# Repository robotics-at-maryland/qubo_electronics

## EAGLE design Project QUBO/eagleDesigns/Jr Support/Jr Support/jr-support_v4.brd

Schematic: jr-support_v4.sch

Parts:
2PIN_1, 2PIN_2, 2PIN_3, 2PIN_5: KK254_VERT_2PIN""; KK254_VERT_2PIN
3V3_LED, 5V_LED, 12V_LED: 0805_LED; 0805
5V_CURR_ADC, 12V_CURR_ADC: ADC121C021; VSSOP-8
5V_OUT: 5V_OUT; KK254_VERT_2PIN
5V_VOLTAGE, 12V_VOLTAGE: INA219SOT23; SOT-23-8
12V_OUT: 12V_OUT; KK254_VERT_2PIN
AUDIO, AUDIO1: KK254_VERT_2PIN""; KK254_VERT_2PIN
BATT1_IN, BATT2_IN: KK254_VERT_2PIN""; KK254_VERT_2PIN
BME280: BME280; BME280_LGA
C1, C2, C5, C7, C8, C10, C11, C13, C14, C16, C17, C19, C21, C22, C23, C33, C46, C47, C59, C64, C69, C70, C71, C72, C73, C74, C77, C79, C80, C81, C84, C94, C101, C103, C104, C106, C107, C109, C110, C112, C113: 0.1u; C0805
C3, C6, C9, C12, C15, C18, C20, C29, C31, C37, C57: 47n; C0805
C4, C27: 0.22u; C0805
C24, C25, C26: 100n; C0805
C28, C65: 22u; C0805
C30: 4.7n; C0805
C34, C35, C36, C60, C66, C93: 1u; C0805
C38, C50: 330 uF; CKR_D10
C40, C51: .1 uF; C0805
C43, C44: 100u; 140CLH-0810
C45, C82, C85: 1n; C0805
C48, C49, C61, C62, C75, C76, C88, C102, C105, C108, C111, C114: 10u; C0805
C53, C78, C83: 4.7u; C0805
CAMERA1, CAMERA2: KK254_VERT_2PIN""; KK254_VERT_2PIN
CIN1, CIN2, CIN3, CIN4: 2.2 uF; C1210
CPU_PWR: CPU PWR; KK254_VERT_4PIN
DEPTH_SENS: Depth Sensor; KK254_VERT_4PIN
ETHERNET: KK254_VERT_2PIN""; KK254_VERT_2PIN
FAN1, FAN2: KK254_VERT_2PIN""; KK254_VERT_2PIN
JP1, JP2: JP1E; JP1
JP3, JP4, JP5, JP6: PINHD-1X2; 1X02
LED1, LED3: Red; 0805
LED4: Green; CHIPLED_0805
LED5, LED8, LED9: Green; 0805
LED6, LED7: Yellow; 0805
PMOS1, PMOS2: SSM3J353F; SOT-346-3/S-MINI
R2, R3: R-TRIMM3314J; RTRIM3314J
R4: 10k; R0805
R5: 21kO; RC55
R6: 2.61kO; RC55
R7, R8: 4.7k; R0805
R9: 12k; R0805
R10, R11: 4.2k; R0805
R12, R15: 5m; R0805
R13: 20.8k; R0805
R14, R23: 51k; R0805
R16, R26: 10\; R0805
R17, R27: 200k; R0805
R19, R28: 8.2k; R0805
R20, R24: 5.1k; R0805
R22: 510; R0805
R25, R30, R35: 10; R0805
R29: 6.8k; R0805
R31: 270; R0805
R32, R50, R51: 1.5k; R0805
R33, R44, R46: 1.2k; R0805
R34: 68; R0805
R36, R41, R45, R47: 1MO; R0805
R37, R42: 430; R0805
R39, R43, R48, R49: 330; R0805
SHORE_IN: KK254_VERT_2PIN""; KK254_VERT_2PIN
TEST-PTS, TEST-PTS1: 0; V526-0
THRUST1, THRUST2, THRUST3, THRUST4, THRUST5, THRUST6, THRUST7, THRUST8: KK254_VERT_4PIN22-29-2041; KK254_VERT_4PIN
THRUSTER_CURR_ADC: ADS7828; TSSOP16
U1: PCA9685; TSSOP-28_4MM
U$1, U$45, U$63, U$64, U$66: VTVSDO-219AB; DO-219AB
U$2, U$4, U$8, U$11, U$14, U$17, U$19, U$23, U$29, U$35, U$39: ACS713SOIC; ACS713-SOIC
U$3, U$54, U$69, U$70, U$71, U$72, U$73, U$74, U$75, U$76: TEST_PT534-5004; 534-5004
U$5: 25A Fuse; 1.25"_FUSECLIPS
U$6, U$9, U$12, U$15, U$18, U$20, U$27, U$36, U$37, U$40: 4A Fuse; 154-OMNI-BLOK
U$7: KUHP-5XX1-XX; KUHP_6.35MM-QUICK-CONNECT
U$10, U$13, U$16, U$21, U$22, U$26, U$28, U$30, U$31, U$32, U$33, U$34, U$38, U$42, U$43, U$44, U$46, U$47, U$62, U$67, U$68: VTVSSOT323; SOT323-R
U$24: BTS5090-1EJA; SOIC8+PAD
U$25, U$41: PTN78060W
U$48, U$51: LTC4364MSOP; MSOP16
U$49, U$50, U$52, U$53: STD95N2LH5; DPAK
U$55, U$58: BSS138CT-NDSOT23; SOT23
U$56: 74LVC1G14; TSSOP5
U$57: NCP1117; SOT-223
U$60, U$61: TL431DBZ; SOT-23-3
V-THRUST_CURR_ADC: ADC121C021; VSSOP-8
V-THRUST_LED: 0805_LED; 0805
V-THRUST_OUT: Vin_OUT; KK254_VERT_2PIN
V-THRUST_VOLTAGE: INA219SOT23; SOT-23-8

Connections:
5V: C36.1, C62.1, JP3.1, R29.2, U$56.P$5 (VDD), U$57.P$2 (VOUT), U$57.P$4 (VOUT)
5V_CURR: C50.P$1 (+), C51.1, U$2.P$1 (IP+), U$2.P$2 (IP+), U$25.P$5 (VO), U$25.P$7 (VOSENSE)
12V_CURR: C38.P$1 (+), C40.1, U$35.P$1 (IP+), U$35.P$2 (IP+), U$41.P$5 (VO), U$41.P$7 (VOSENSE)
+3V3: 2PIN_2.P$1, BME280.P$2 (!CS), BME280.P$5 (SDO/ADR), BME280.P$6 (VDDIO), BME280.P$8 (VDD), C24.1, C25.1, C26.1, C83.1, C84.1, C85.1, R10.2, R11.2, R34.2, U$3.P$1
+5V: 2PIN_1.P$1, 2PIN_3.P$1, 5V_CURR_ADC.P$5 (VDD), 5V_CURR_ADC.P$6 (ADR1), 5V_OUT.P$1, 5V_VOLTAGE.P$4 (VS), 12V_CURR_ADC.P$5 (VDD), 12V_VOLTAGE.P$4 (VS), 12V_VOLTAGE.P$8 (A1), C1.1, C2.1, C5.1, C7.1, C8.1, C11.1, C13.1, C14.1, C19.1, C48.1, C53.1, C59.1, C64.1, C66.1, C69.1, C70.1, C71.1, C72.1, C73.1, C79.1, C81.1, C82.1, C93.1, C94.1, C103.1, C106.1, C109.1, C112.1, DEPTH_SENS.P$4, ETHERNET.P$1, FAN1.P$1, FAN2.P$1, R7.2, R8.2, R31.2, R35.1, THRUSTER_CURR_ADC.10 (REF), THRUSTER_CURR_ADC.16 (VDD), U1.1 (A0), U1.2 (A1), U1.3 (A2), U1.4 (A3), U1.5 (A4), U1.24 (A5), U1.28 (VDD), U$2.P$8 (VCC), U$4.P$8 (VCC), U$8.P$8 (VCC), U$11.P$8 (VCC), U$14.P$8 (VCC), U$17.P$8 (VCC), U$19.P$8 (VCC), U$20.P$2, U$21.1 (C), U$21.2 (C), U$23.P$8 (VCC), U$29.P$8 (VCC), U$35.P$8 (VCC), U$39.P$8 (VCC), U$42.1 (C), U$42.2 (C), U$43.1 (C), U$43.2 (C), U$44.1 (C), U$44.2 (C), U$46.1 (C), U$46.2 (C), U$47.1 (C), U$47.2 (C), U$69.P$1, V-THRUST_CURR_ADC.P$3 (ADR0), V-THRUST_CURR_ADC.P$5 (VDD), V-THRUST_CURR_ADC.P$6 (ADR1), V-THRUST_VOLTAGE.P$4 (VS), V-THRUST_VOLTAGE.P$7 (A0), V-THRUST_VOLTAGE.P$8 (A1)
+12V: 12V_OUT.P$1, C16.1, C33.1, C45.1, C49.1, C77.1, C78.1, CPU_PWR.P$3, CPU_PWR.P$4, JP4.1, R25.1, R33.2, U$1.P$2 (C), U$24.PAD (VS), U$36.P$2, U$63.P$2 (C), U$64.P$2 (C), U$70.P$1
GND: 2PIN_2.P$2, 2PIN_3.P$2, 2PIN_5.P$2, 3V3_LED.P$2 (C), 5V_CURR_ADC.P$3 (ADR0), 5V_CURR_ADC.P$7 (GND), 5V_LED.P$2 (C), 5V_OUT.P$2, 5V_VOLTAGE.P$3 (GND), 5V_VOLTAGE.P$7 (A0), 5V_VOLTAGE.P$8 (A1), 12V_CURR_ADC.P$3 (ADR0), 12V_CURR_ADC.P$6 (ADR1), 12V_CURR_ADC.P$7 (GND), 12V_LED.P$2 (C), 12V_OUT.P$2, 12V_VOLTAGE.P$3 (GND), 12V_VOLTAGE.P$7 (A0), AUDIO.P$2, AUDIO1.P$2, BATT1_IN.P$2, BATT2_IN.P$2, BME280.P$1 (GND1), BME280.P$7 (GND2), C1.2, C2.2, C3.2, C4.2, C5.2, C6.2, C7.2, C8.2, C9.2, C10.2, C11.2, C12.2, C13.2, C14.2, C15.2, C16.2, C17.2, C18.2, C19.2, C20.2, C21.2, C22.2, C23.2, C24.2, C25.2, C26.2, C27.2, C28.2, C29.2, C30.2, C31.2, C33.2, C34.2, C35.2, C36.2, C37.2, C38.P$2 (-), C40.2, C43.-, C44.-, C45.2, C46.2, C47.2, C48.2, C49.2, C50.P$2 (-), C51.2, C53.2, C57.2, C59.2, C60.2, C61.2, C62.2, C64.2, C65.2, C66.2, C69.2, C70.2, C71.2, C72.2, C73.2, C74.2, C75.2, C76.2, C77.2, C78.2, C79.2, C80.2, C81.2, C82.2, C83.2, C84.2, C85.2, C88.2, C93.2, C94.2, C101.2, C102.2, C103.2, C104.2, C105.2, C106.2, C107.2, C108.2, C109.2, C110.2, C111.2, C112.2, C113.2, C114.2, CAMERA1.P$2, CAMERA2.P$2, CIN1.2, CIN2.2, CIN3.2, CIN4.2, CPU_PWR.P$1, CPU_PWR.P$2, DEPTH_SENS.P$3, ETHERNET.P$2, FAN1.P$2, FAN2.P$2, JP1.1, JP2.1, LED1.P$2 (C), LED3.P$2 (C), LED6.P$2 (C), LED7.P$2 (C), LED8.P$2 (C), LED9.P$2 (C), R2.1 (E), R3.1 (E), R4.1, R5.P$2 (2), R6.P$2 (2), R9.1, R13.1, R20.1, R24.1, SHORE_IN.P$2, TEST-PTS.1, TEST-PTS1.1, THRUST1.P$1, THRUST1.P$3, THRUST2.P$1, THRUST2.P$3, THRUST3.P$1, THRUST3.P$3, THRUST4.P$1, THRUST4.P$3, THRUST5.P$1, THRUST5.P$3, THRUST6.P$1, THRUST6.P$3, THRUST7.P$1, THRUST7.P$3, THRUST8.P$1, THRUST8.P$3, THRUSTER_CURR_ADC.9 (GND), THRUSTER_CURR_ADC.11 (COM), THRUSTER_CURR_ADC.12 (A0), THRUSTER_CURR_ADC.13 (A1), U1.14 (VSS), U1.23 (!OE), U1.25 (EXTCLK), U$1.P$1 (A), U$2.P$5 (GND), U$4.P$5 (GND), U$7.5A (5), U$7.5B (5), U$7.BA (B), U$7.BB (B), U$8.P$5 (GND), U$10.3 (A), U$11.P$5 (GND), U$13.3 (A), U$14.P$5 (GND), U$16.3 (A), U$17.P$5 (GND), U$19.P$5 (GND), U$22.3 (A), U$23.P$5 (GND), U$24.1 (GND), U$25.P$1 (GND1), U$25.P$2 (GND2), U$26.3 (A), U$28.3 (A), U$29.P$5 (GND), U$30.3 (A), U$31.3 (A), U$32.3 (A), U$33.3 (A), U$34.3 (A), U$35.P$5 (GND), U$38.3 (A), U$39.P$5 (GND), U$41.P$1 (GND1), U$41.P$2 (GND2), U$42.3 (A), U$43.3 (A), U$44.3 (A), U$45.P$1 (A), U$46.3 (A), U$47.3 (A), U$48.GND, U$48.OV, U$51.GND, U$51.OV, U$55.2 (S), U$56.P$3 (GND), U$57.P$1 (GND), U$58.2 (S), U$60.P$3 (A), U$61.P$3 (A), U$62.3 (A), U$63.P$1 (A), U$64.P$1 (A), U$66.P$1 (A), U$67.3 (A), U$68.3 (A), V-THRUST_CURR_ADC.P$7 (GND), V-THRUST_LED.P$2 (C), V-THRUST_OUT.P$2, V-THRUST_VOLTAGE.P$3 (GND)
unnamed: R26.1, U$48.HGATE
unnamed: C30.1, JP4.2, U$7.AA (A), U$7.AB (A), U$24.6 (OUT), U$24.7 (OUT), U$24.8 (OUT), U$45.P$2 (C)
unnamed: JP2.2, U$41.P$3 (!INHIBIT!)
unnamed: 2PIN_1.P$2, C23.1, R4.2, U$21.3 (A), U$24.2 (IN)
unnamed: R6.P$1 (1), U$41.P$6 (VOADJUST)
unnamed: C3.1, U$2.P$6 (FILTER)
unnamed: C9.1, U$8.P$6 (FILTER)
unnamed: C6.1, U$4.P$6 (FILTER)
unnamed: JP1.2, U$25.P$3 (!INHIBIT!)
unnamed: U$4.P$3 (IP-), U$4.P$4 (IP-), U$6.P$1
unnamed: R5.P$1 (1), U$25.P$6 (VOADJUST)
unnamed: U$8.P$3 (IP-), U$8.P$4 (IP-), U$9.P$1
unnamed: C12.1, U$11.P$6 (FILTER)
unnamed: C4.1, U$48.TMR
unnamed: U$11.P$3 (IP-), U$11.P$4 (IP-), U$12.P$1
unnamed: C15.1, U$14.P$6 (FILTER)
unnamed: R23.2, R28.1
unnamed: R26.2, U$49.1 (G)
unnamed: U$14.P$3 (IP-), U$14.P$4 (IP-), U$15.P$1
unnamed: C18.1, U$17.P$6 (FILTER)
unnamed: R12.1, U$48.SENSE, U$50.TAB (D)
unnamed: U$17.P$3 (IP-), U$17.P$4 (IP-), U$18.P$1
unnamed: C29.1, U$23.P$6 (FILTER)
unnamed: U$48.DGATE, U$50.1 (G)
unnamed: U$23.P$3 (IP-), U$23.P$4 (IP-), U$27.P$1
unnamed: C37.1, U$29.P$6 (FILTER)
unnamed: C20.1, U$19.P$6 (FILTER)
unnamed: U$5.P$1, U$5.P$2, U$19.P$3 (IP-), U$19.P$4 (IP-)
unnamed: R13.2, R17.1, U$51.UV
unnamed: R14.1, R20.2, U$51.FB
unnamed: U$29.P$3 (IP-), U$29.P$4 (IP-), U$37.P$1
unnamed: C57.1, U$39.P$6 (FILTER)
unnamed: R9.2, R27.1, U$48.UV
unnamed: R16.1, U$51.HGATE
unnamed: C27.1, U$51.TMR
unnamed: R14.2, R19.1
unnamed: R16.2, U$52.1 (G)
unnamed: U$51.SOURCE, U$52.3 (S), U$53.3 (S)
unnamed: R15.1, U$51.SENSE, U$53.TAB (D)
unnamed: U$39.P$3 (IP-), U$39.P$4 (IP-), U$40.P$1
unnamed: U$51.DGATE, U$53.1 (G)
unnamed: 12V_VOLTAGE.P$1 (IN+), 12V_VOLTAGE.P$2 (IN-), R25.2
unnamed: R23.1, R24.2, U$48.FB
unnamed: C60.1, R22.2, U$56.P$2 (IN)
unnamed: C31.1, U$35.P$6 (FILTER)
unnamed: U$19.P$7 (VIOUT), V-THRUST_CURR_ADC.P$4 (VIN)
unnamed: U$48.SOURCE, U$49.3 (S), U$50.3 (S)
unnamed: U$2.P$3 (IP-), U$2.P$4 (IP-), U$20.P$1
unnamed: U$35.P$3 (IP-), U$35.P$4 (IP-), U$36.P$1
unnamed: 5V_CURR_ADC.P$4 (VIN), U$2.P$7 (VIOUT)
unnamed: R30.2, V-THRUST_VOLTAGE.P$1 (IN+), V-THRUST_VOLTAGE.P$2 (IN-)
unnamed: 12V_CURR_ADC.P$4 (VIN), U$35.P$7 (VIOUT)
unnamed: JP3.2, U$48.SHDN (!SHDN!), U$51.SHDN (!SHDN!), U$56.P$4 (OUT)
unnamed: LED1.P$1 (A), R37.1
unnamed: PMOS1.P$1 (G), R36.1, U$51.FLT (!FAULT!)
unnamed: AUDIO.P$1, R37.2, R39.1
unnamed: LED3.P$1 (A), R42.1
unnamed: PMOS2.P$1 (G), R41.1, U$48.FLT (!FAULT!)
unnamed: AUDIO1.P$1, R42.2, R43.1
unnamed: R44.1, U$55.3 (D)
unnamed: LED4.C, R44.2
unnamed: 5V_LED.P$1 (A), R31.1
unnamed: R32.1, V-THRUST_LED.P$1 (A)
unnamed: 12V_LED.P$1 (A), R33.1
unnamed: 3V3_LED.P$1 (A), R34.1
unnamed: R46.1, U$58.3 (D)
unnamed: LED5.P$2 (C), R46.2
unnamed: 5V_VOLTAGE.P$1 (IN+), 5V_VOLTAGE.P$2 (IN-), R35.2
unnamed: R2.2 (S), TEST-PTS.2, U$60.P$2 (REF)
unnamed: LED6.P$1 (A), R48.1, U$60.P$1 (C)
unnamed: R3.2 (S), TEST-PTS1.2, U$61.P$2 (REF)
unnamed: LED7.P$1 (A), R49.1, U$61.P$1 (C)
unnamed: R47.1, U$51.ENOUT, U$58.1 (G)
unnamed: R45.1, U$48.ENOUT, U$55.1 (G)
unnamed: LED8.P$1 (A), R50.1
unnamed: LED9.P$1 (A), R51.1
unnamed: PMOS1.P$2 (D), R39.2
unnamed: PMOS2.P$2 (D), R43.2
SCL: 5V_CURR_ADC.P$1 (SCL), 5V_VOLTAGE.P$5 (SCL), 12V_CURR_ADC.P$1 (SCL), 12V_VOLTAGE.P$5 (SCL), JP5.2, R8.1, THRUSTER_CURR_ADC.14 (SCL), U1.26 (SCL), U$71.P$1, V-THRUST_CURR_ADC.P$1 (SCL), V-THRUST_VOLTAGE.P$5 (SCL)
SCL-3V3: BME280.P$4 (SCK/SCL), DEPTH_SENS.P$1, JP6.2, R11.1
SDA: 5V_CURR_ADC.P$8 (SDA), 5V_VOLTAGE.P$6 (SDA), 12V_CURR_ADC.P$8 (SDA), 12V_VOLTAGE.P$6 (SDA), JP5.1, R7.1, THRUSTER_CURR_ADC.15 (SDA), U1.27 (SDA), U$72.P$1, V-THRUST_CURR_ADC.P$8 (SDA), V-THRUST_VOLTAGE.P$6 (SDA)
SDA-3V3: BME280.P$3 (SDI/SDA), DEPTH_SENS.P$2, JP6.1, R10.1
SHDN_SW: 2PIN_5.P$1, R22.1, R29.1, U$62.1 (C), U$62.2 (C)
T1_CURR: THRUSTER_CURR_ADC.1 (CH0), U$4.P$7 (VIOUT)
T1_PWM: THRUST1.P$2, U1.6 (CH0)
T2_CURR: THRUSTER_CURR_ADC.2 (CH1), U$8.P$7 (VIOUT)
T2_PWM: THRUST2.P$2, U1.7 (CH1)
T3_CURR: THRUSTER_CURR_ADC.3 (CH2), U$11.P$7 (VIOUT)
T3_PWM: THRUST3.P$2, U1.8 (CH2)
T4_CURR: THRUSTER_CURR_ADC.4 (CH3), U$14.P$7 (VIOUT)
T4_PWM: THRUST4.P$2, U1.9 (CH3)
T5_CURR: THRUSTER_CURR_ADC.5 (CH4), U$17.P$7 (VIOUT)
T5_PWM: THRUST5.P$2, U1.10 (CH4)
T6_CURR: THRUSTER_CURR_ADC.6 (CH5), U$23.P$7 (VIOUT)
T6_PWM: THRUST6.P$2, U1.11 (CH5)
T7_CURR: THRUSTER_CURR_ADC.7 (CH6), U$29.P$7 (VIOUT)
T7_PWM: THRUST7.P$2, U1.12 (CH6)
T8_CURR: THRUSTER_CURR_ADC.8 (CH7), U$39.P$7 (VIOUT)
T8_PWM: THRUST8.P$2, U1.13 (CH7)
VIN: C28.1, C65.1, CIN1.1, CIN2.1, CIN3.1, CIN4.1, R12.2, R15.2, R19.2, R28.2, SHORE_IN.P$1, U$7.2A (2), U$7.2B (2), U$25.P$4 (VI), U$41.P$4 (VI), U$48.OUT, U$51.OUT, U$66.P$2 (C), U$73.P$1
V_BATT1: BATT1_IN.P$1, C34.1, C61.1, LED4.A, PMOS2.P$3 (S), R3.3 (A), R27.2, R41.2, R45.2, R49.2, R51.2, U$48.VCC, U$49.TAB (D), U$57.P$3 (VIN), U$68.1 (C), U$68.2 (C), U$75.P$1
V_BATT2: BATT2_IN.P$1, C35.1, LED5.P$1 (A), PMOS1.P$3 (S), R2.3 (A), R17.2, R36.2, R47.2, R48.2, R50.2, U$51.VCC, U$52.TAB (D), U$67.1 (C), U$67.2 (C), U$74.P$1
V_RELAY: U$7.7A (7), U$7.7B (7), U$19.P$1 (IP+), U$19.P$2 (IP+)
V_THRUST: C17.1, C21.1, C22.1, C43.+, C44.+, C46.1, C47.1, CAMERA1.P$1, CAMERA2.P$1, R30.1, R32.2, U$4.P$1 (IP+), U$4.P$2 (IP+), U$5.P$3, U$5.P$4, U$8.P$1 (IP+), U$8.P$2 (IP+), U$11.P$1 (IP+), U$11.P$2 (IP+), U$14.P$1 (IP+), U$14.P$2 (IP+), U$17.P$1 (IP+), U$17.P$2 (IP+), U$23.P$1 (IP+), U$23.P$2 (IP+), U$29.P$1 (IP+), U$29.P$2 (IP+), U$32.1 (C), U$32.2 (C), U$33.1 (C), U$33.2 (C), U$34.1 (C), U$34.2 (C), U$38.1 (C), U$38.2 (C), U$39.P$1 (IP+), U$39.P$2 (IP+), U$54.P$1, U$76.P$1, V-THRUST_OUT.P$1
V_THRUST1: THRUST1.P$4, U$6.P$2, U$31.1 (C), U$31.2 (C)
V_THRUST2: C10.1, C74.1, C75.1, C76.1, THRUST2.P$4, U$9.P$2, U$30.1 (C), U$30.2 (C)
V_THRUST3: C107.1, C108.1, THRUST3.P$4, U$12.P$2, U$26.1 (C), U$26.2 (C)
V_THRUST4: C80.1, C88.1, THRUST4.P$4, U$15.P$2, U$28.1 (C), U$28.2 (C)
V_THRUST5: C110.1, C111.1, THRUST5.P$4, U$18.P$2, U$22.1 (C), U$22.2 (C)
V_THRUST6: C101.1, C102.1, THRUST6.P$4, U$13.1 (C), U$13.2 (C), U$27.P$2
V_THRUST7: C113.1, C114.1, THRUST7.P$4, U$16.1 (C), U$16.2 (C), U$37.P$2
V_THRUST8: C104.1, C105.1, THRUST8.P$4, U$10.1 (C), U$10.2 (C), U$40.P$2

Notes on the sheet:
Address: 1110111 (0x77)(BME)
Address: 1001000 (Thrust ADC)
Address: 1010101 (12V ADC)
Address: 1011010 (VIN ADC)
Address: 1011001 (5V ADC)
12V DC/DC Converter
12V Current Sensor and 12V Net
12V Voltage sensor
12V Rail
5V Voltage Sensor
5V Current Sensor and 5V Net
5V DC/DC Converter
5V Rail
V_Thrust Rail
V_Thrust Current Sensor and V_Thrust Net
V_Thrust Voltage Sensor
Thrusters
Thruster Support
Pulling Rs
LEDs
Input Voltage
Temp Sensor
External Connectors
Thruster Relay
The blue LED will turn on when the battery voltage drops below a level given by: (2.5V)(10kO) ----------------- POT where POT is the resistance of the potentiometer.
Embedded System Headers

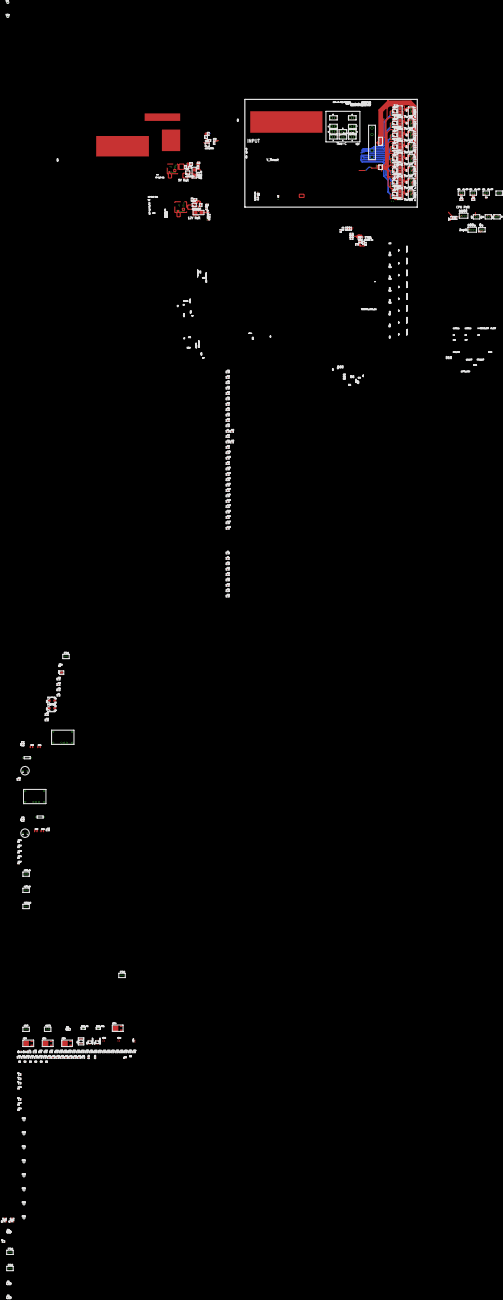
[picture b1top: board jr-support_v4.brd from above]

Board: 2 copper layers, 203.2 x 127.0 mm, 272 parts (0 on the bottom side), 119 nets.

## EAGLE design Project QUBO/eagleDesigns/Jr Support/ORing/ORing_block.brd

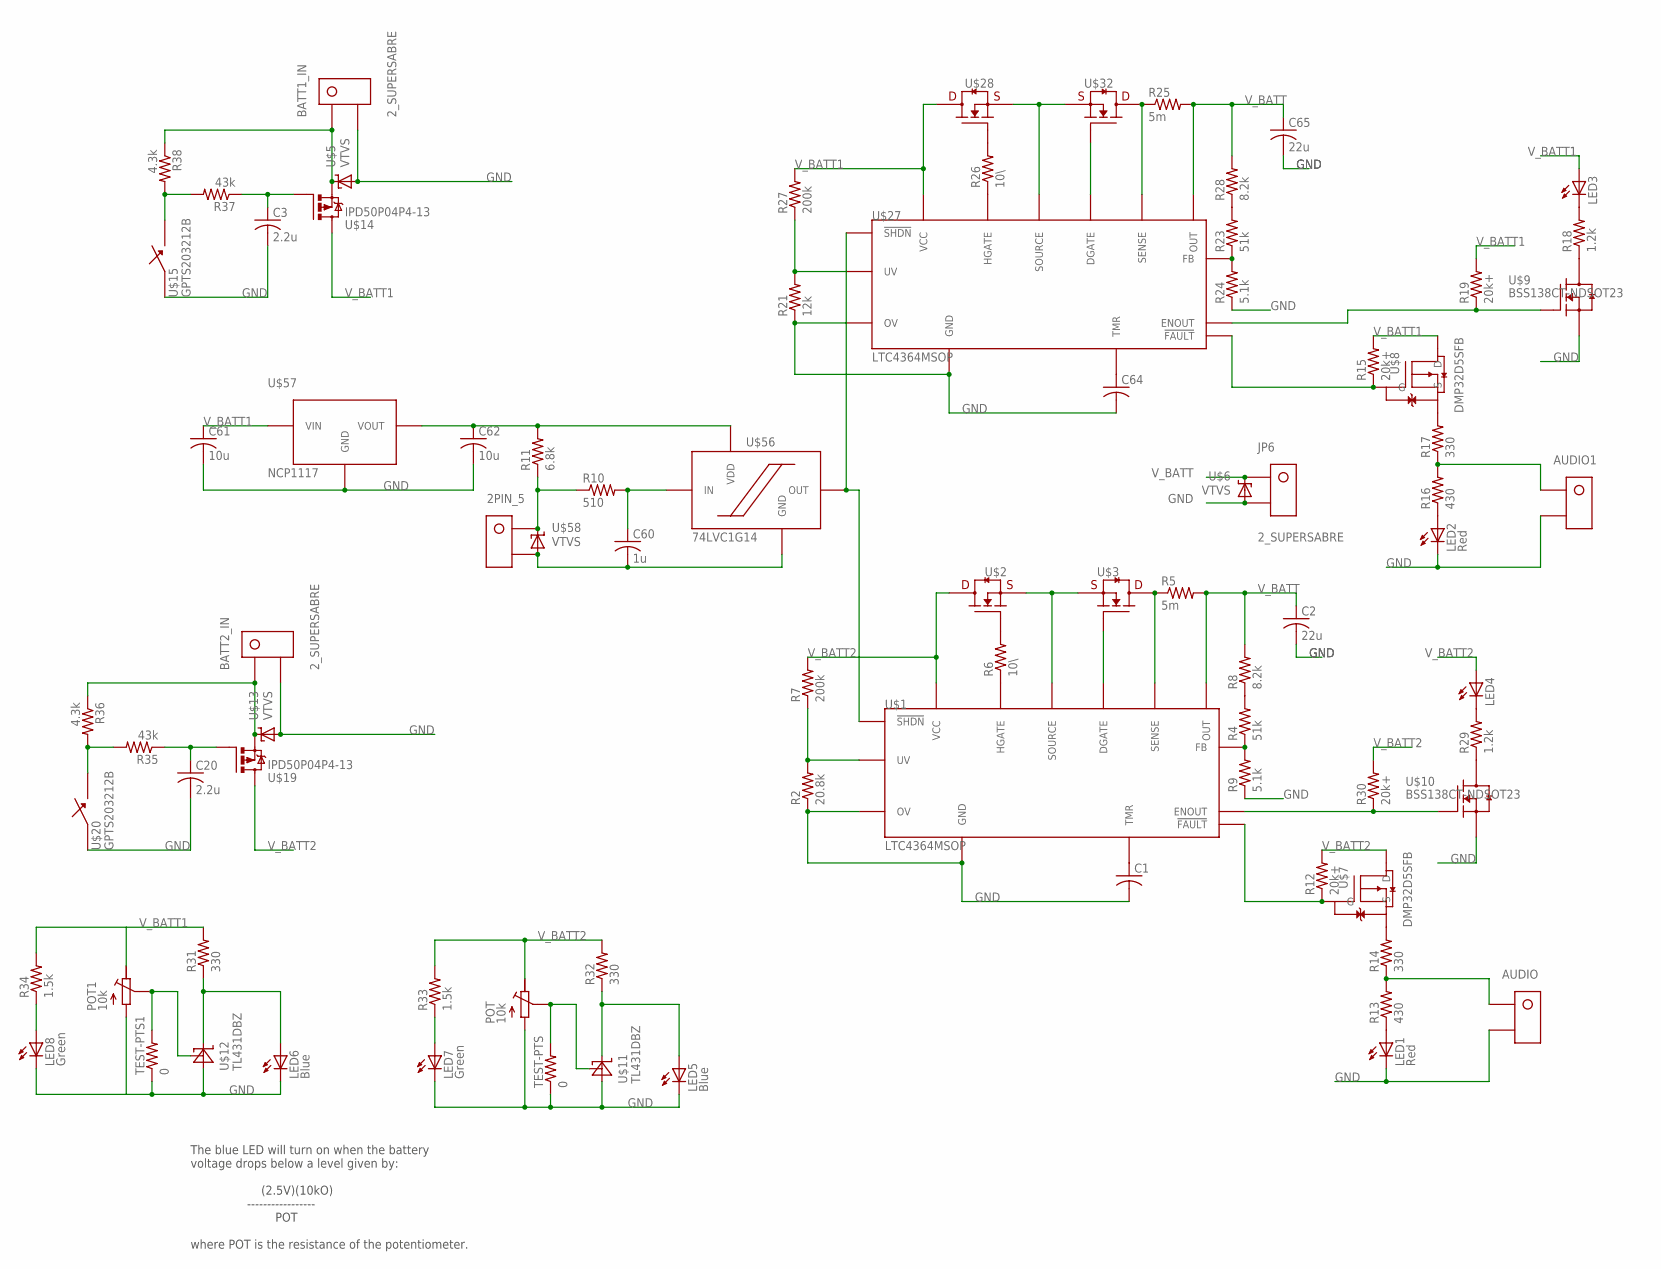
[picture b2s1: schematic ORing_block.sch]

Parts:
2PIN_5: KK254_VERT_2PIN22-29-2021; KK254_VERT_2PIN
AUDIO, AUDIO1: KK254_VERT_2PIN22-29-2021; KK254_VERT_2PIN
BATT1_IN, BATT2_IN: 2_SUPERSABRE; SUPERSABRE_2CIRCUIT
C1, C64: C-USC0805; C0805
C2, C65: 22u; C0805
C3, C20: 2.2u; C0805
C60: 1u; C0805
C61, C62: 10u; C0805
JP6: 2_SUPERSABRE; SUPERSABRE_2CIRCUIT
LED1, LED2: Red; CHIPLED_0805
LED3, LED4: LEDCHIPLED_0805; CHIPLED_0805
LED5, LED6: Blue; 0805
LED7, LED8: Green; 0805
POT, POT1: 10k; PTV09A-4
R2: 20.8k; R0805
R4, R23: 51k; R0805
R5, R25: 5m; R0805
R6, R26: 10\; R0805
R7, R27: 200k; R0805
R8, R28: 8.2k; R0805
R9, R24: 5.1k; R0805
R10: 510; R0805
R11: 6.8k; R0805
R12, R15, R19, R30: 20k+; R0805
R13, R16: 430; R0805
R14, R17, R31, R32: 330; R0805
R18, R29: 1.2k; R0805
R21: 12k; R0805
R33, R34: 1.5k; R0805
R35, R37: 43k; R0805
R36, R38: 4.3k; R0805
TEST-PTS, TEST-PTS1: 0; V526-0
U$1, U$27: LTC4364MSOP; MSOP16
U$2, U$3, U$28, U$32: FDMC8360LET40PWR33; POWER33
U$5, U$6, U$13, U$58: VTVS; DO-219AB
U$7, U$8: DMP32D5SFB; AP02002
U$9, U$10: BSS138CT-NDSOT23; SOT23
U$11, U$12: TL431DBZ; SOT-23-3
U$14, U$19: IPD50P04P4-13; TO252-3
U$15, U$20: GPTS203212B; GPTS203211B
U$56: 74LVC1G14; TSSOP5
U$57: NCP1117; SOT-223

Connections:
GND: AUDIO.P$2, AUDIO1.P$2, BATT1_IN.P$2, BATT2_IN.P$2, C1.2, C2.2, C3.2, C20.2, C61.2, C62.2, C64.2, C65.2, JP6.P$2, LED1.C, LED2.C, LED5.P$2 (C), LED6.P$2 (C), LED7.P$2 (C), LED8.P$2 (C), POT.P$3 (E), POT1.P$3 (E), R2.1, R9.1, R21.1, R24.1, TEST-PTS.1, TEST-PTS1.1, U$1.GND, U$1.OV, U$5.P$1 (A), U$6.P$1 (A), U$9.2 (S), U$10.2 (S), U$11.P$3 (A), U$12.P$3 (A), U$13.P$1 (A), U$15.P$1, U$20.P$1, U$27.GND, U$27.OV, U$57.P$1 (GND)
unnamed: R2.2, R7.1, U$1.UV
unnamed: R4.1, R9.2, U$1.FB
unnamed: R6.1, U$1.HGATE
unnamed: C1.1, U$1.TMR
unnamed: R4.2, R8.1
unnamed: R6.2, U$2.GATE
unnamed: U$1.SOURCE, U$2.SOURCE1 (SOURCE), U$2.SOURCE2 (SOURCE), U$2.SOURCE3 (SOURCE), U$3.SOURCE1 (SOURCE), U$3.SOURCE2 (SOURCE), U$3.SOURCE3 (SOURCE)
unnamed: R5.1, U$1.SENSE, U$3.DRAIN
unnamed: U$1.DGATE, U$3.GATE
unnamed: 2PIN_5.P$1, R10.1, R11.1, U$58.P$2 (C)
unnamed: C62.1, R11.2, U$56.P$5 (VDD), U$57.P$2 (VOUT), U$57.P$4 (VOUT)
unnamed: U$1.SHDN (!SHDN!), U$27.SHDN (!SHDN!), U$56.P$4 (OUT)
unnamed: R14.2, U$7.P$1 (S)
unnamed: LED1.A, R13.1
unnamed: R12.1, U$1.FLT (!FAULT!), U$7.P$2 (G)
unnamed: AUDIO.P$1, R13.2, R14.1
unnamed: LED2.A, R16.1
unnamed: R15.1, U$8.P$2 (G), U$27.FLT (!FAULT!)
unnamed: R17.2, U$8.P$1 (S)
unnamed: AUDIO1.P$1, R16.2, R17.1
unnamed: POT.P$2 (S), TEST-PTS.2, U$11.P$2 (REF)
unnamed: R18.1, U$9.3 (D)
unnamed: LED3.C, R18.2
unnamed: R29.1, U$10.3 (D)
unnamed: LED4.C, R29.2
unnamed: R30.1, U$1.ENOUT, U$10.1 (G)
unnamed: R19.1, U$9.1 (G), U$27.ENOUT
unnamed: LED5.P$1 (A), R32.1, U$11.P$1 (C)
unnamed: POT1.P$2 (S), TEST-PTS1.2, U$12.P$2 (REF)
unnamed: LED6.P$1 (A), R31.1, U$12.P$1 (C)
unnamed: LED7.P$1 (A), R33.1
unnamed: LED8.P$1 (A), R34.1
unnamed: C20.1, R35.1, U$19.1 (G)
unnamed: R35.2, R36.2, U$20.P$2
unnamed: R26.1, U$27.HGATE
unnamed: BATT1_IN.P$1, R38.1, U$5.P$2 (C), U$14.TAB (D)
unnamed: R21.2, R27.1, U$27.UV
unnamed: C3.1, R37.1, U$14.1 (G)
unnamed: R37.2, R38.2, U$15.P$2
unnamed: BATT2_IN.P$1, R36.1, U$13.P$2 (C), U$19.TAB (D)
unnamed: 2PIN_5.P$2, C60.2, U$56.P$3 (GND), U$58.P$1 (A)
unnamed: C60.1, R10.2, U$56.P$2 (IN)
unnamed: R23.1, R24.2, U$27.FB
unnamed: C64.1, U$27.TMR
unnamed: U$27.SOURCE, U$28.SOURCE1 (SOURCE), U$28.SOURCE2 (SOURCE), U$28.SOURCE3 (SOURCE), U$32.SOURCE1 (SOURCE), U$32.SOURCE2 (SOURCE), U$32.SOURCE3 (SOURCE)
unnamed: R23.2, R28.1
unnamed: R26.2, U$28.GATE
unnamed: R25.1, U$27.SENSE, U$32.DRAIN
unnamed: U$27.DGATE, U$32.GATE
V_BATT: C2.1, C65.1, JP6.P$1, R5.2, R8.2, R25.2, R28.2, U$1.OUT, U$6.P$2 (C), U$27.OUT
V_BATT1: C61.1, LED3.A, POT1.P$1 (A), R15.2, R19.2, R27.2, R31.2, R34.2, U$8.P$3 (D), U$14.3 (S), U$27.VCC, U$28.DRAIN, U$57.P$3 (VIN)
V_BATT2: LED4.A, POT.P$1 (A), R7.2, R12.2, R30.2, R32.2, R33.2, U$1.VCC, U$2.DRAIN, U$7.P$3 (D), U$19.3 (S)

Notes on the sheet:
The blue LED will turn on when the battery voltage drops below a level given by: (2.5V)(10kO) ----------------- POT where POT is the resistance of the potentiometer.

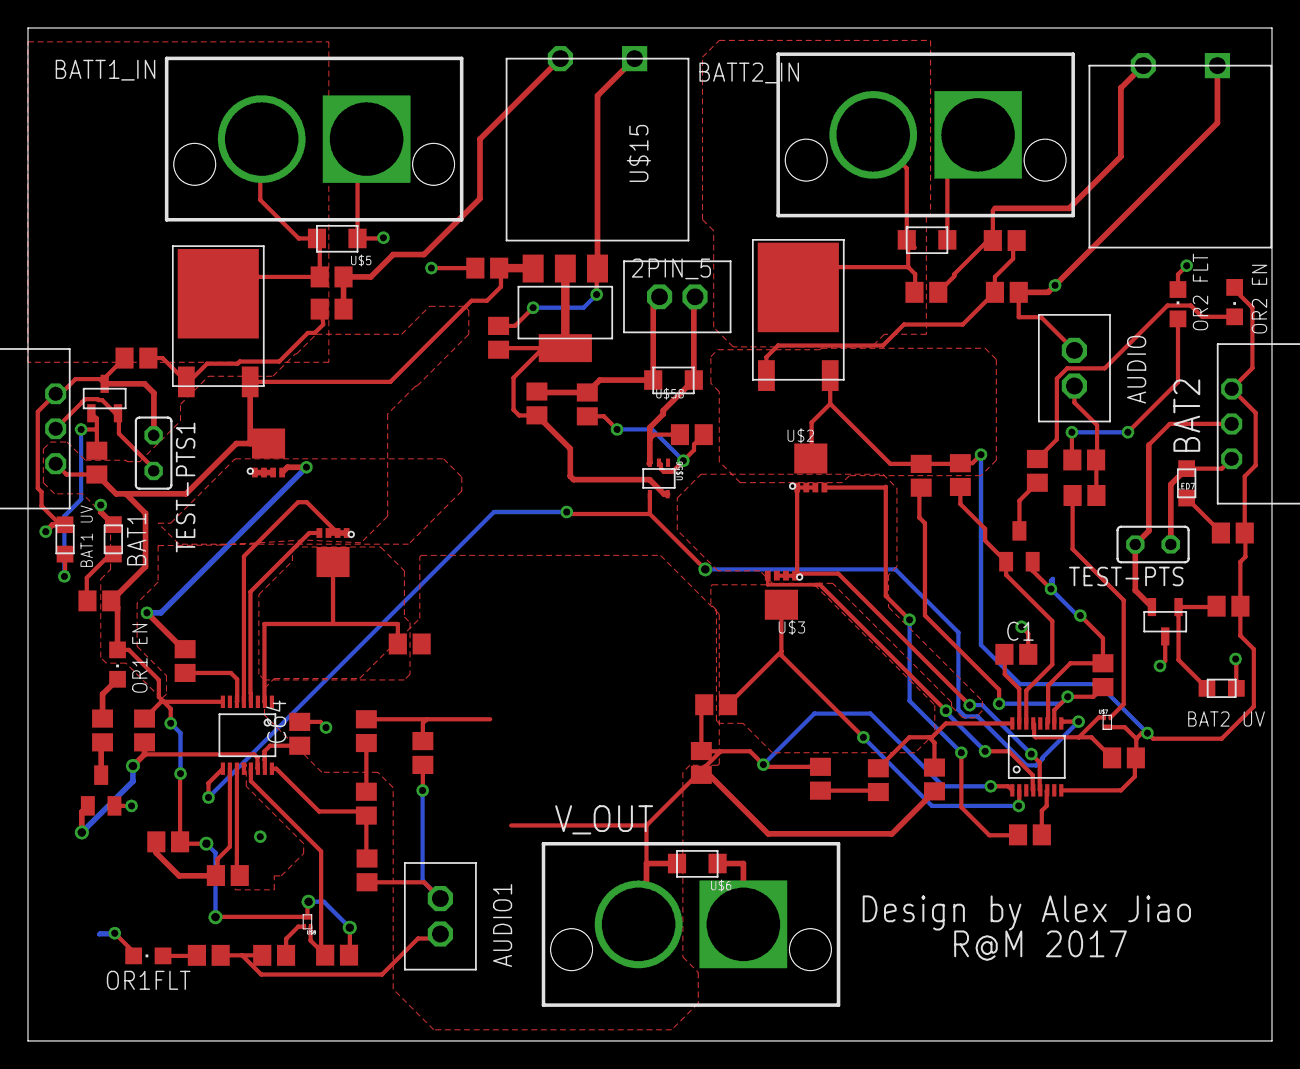
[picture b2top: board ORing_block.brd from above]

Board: 2 copper layers, 88.9 x 72.4 mm, 83 parts (0 on the bottom side), 53 nets.

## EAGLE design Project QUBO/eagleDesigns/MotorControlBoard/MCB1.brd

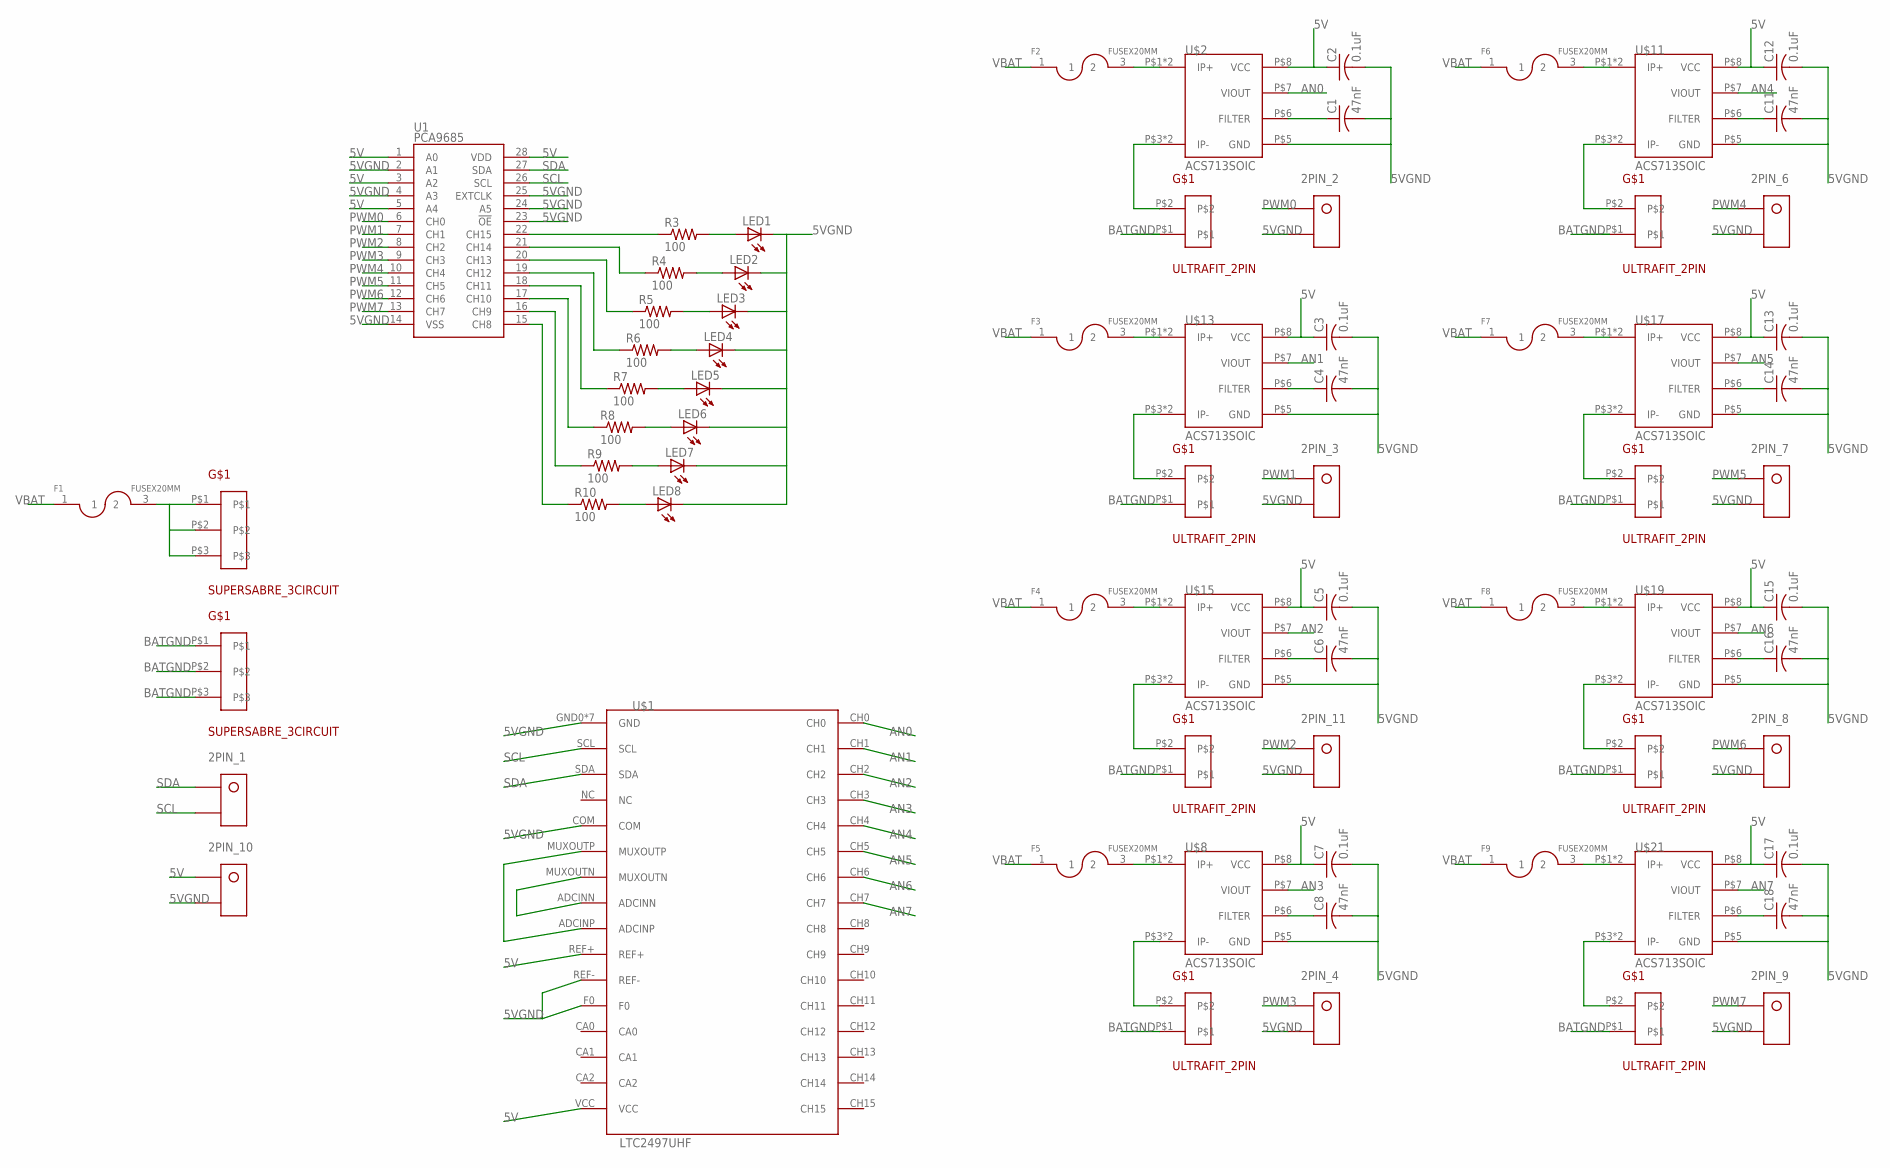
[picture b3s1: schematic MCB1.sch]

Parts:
2PIN_1, 2PIN_2, 2PIN_3, 2PIN_4, 2PIN_6, 2PIN_7, 2PIN_8, 2PIN_9, 2PIN_10, 2PIN_11: KK254_VERT_2PIN22-29-2021; KK254_VERT_2PIN
C1, C4, C6, C8, C11, C14, C16, C18: 47nF; C0805
C2, C3, C5, C7, C12, C13, C15, C17: 0.1uF; C0805
F1, F2, F3, F4, F5, F6, F7, F8, F9: FUSEX20MM; FUSE_5MM
LED1, LED2, LED3, LED4, LED5, LED6, LED7, LED8: LEDCHIPLED_0805; CHIPLED_0805
R3, R4, R5, R6, R7, R8, R9, R10: 100; R0805
U1: PCA9685; TSSOP-28_4MM
U$1: LTC2497UHF; LTC2497-UHF
U$2, U$8, U$11, U$13, U$15, U$17, U$19, U$21: ACS713SOIC; ACS713-SOIC
U$3, U$4: SUPERSABRE_3CIRCUIT
U$5, U$6, U$7, U$12, U$14, U$16, U$18, U$20: ULTRAFIT_2PIN

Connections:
5V: 2PIN_10.P$1, C2.1, C3.1, C5.1, C7.1, C12.1, C13.1, C15.1, C17.1, U1.1 (A0), U1.3 (A2), U1.5 (A4), U1.28 (VDD), U$1.REF+, U$1.VCC, U$2.P$8 (VCC), U$8.P$8 (VCC), U$11.P$8 (VCC), U$13.P$8 (VCC), U$15.P$8 (VCC), U$17.P$8 (VCC), U$19.P$8 (VCC), U$21.P$8 (VCC)
5VGND: 2PIN_2.P$2, 2PIN_3.P$2, 2PIN_4.P$2, 2PIN_6.P$2, 2PIN_7.P$2, 2PIN_8.P$2, 2PIN_9.P$2, 2PIN_10.P$2, 2PIN_11.P$2, C1.2, C2.2, C3.2, C4.2, C5.2, C6.2, C7.2, C8.2, C11.2, C12.2, C13.2, C14.2, C15.2, C16.2, C17.2, C18.2, LED1.C, LED2.C, LED3.C, LED4.C, LED5.C, LED6.C, LED7.C, LED8.C, U1.2 (A1), U1.4 (A3), U1.14 (VSS), U1.23 (!OE), U1.24 (A5), U1.25 (EXTCLK), U$1.COM, U$1.F0, U$1.GND0 (GND), U$1.GND1 (GND), U$1.GND2 (GND), U$1.GND3 (GND), U$1.GND4 (GND), U$1.GND5 (GND), U$1.GND6 (GND), U$1.REF-, U$2.P$5 (GND), U$8.P$5 (GND), U$11.P$5 (GND), U$13.P$5 (GND), U$15.P$5 (GND), U$17.P$5 (GND), U$19.P$5 (GND), U$21.P$5 (GND)
AN0: U$1.CH0, U$2.P$7 (VIOUT)
AN1: U$1.CH1, U$13.P$7 (VIOUT)
AN2: U$1.CH2, U$15.P$7 (VIOUT)
AN3: U$1.CH3, U$8.P$7 (VIOUT)
AN4: U$1.CH4, U$11.P$7 (VIOUT)
AN5: U$1.CH5, U$17.P$7 (VIOUT)
AN6: U$1.CH6, U$19.P$7 (VIOUT)
AN7: U$1.CH7, U$21.P$7 (VIOUT)
BATGND: U$3.P$1, U$3.P$2, U$3.P$3, U$5.P$1, U$6.P$1, U$7.P$1, U$12.P$1, U$14.P$1, U$16.P$1, U$18.P$1, U$20.P$1
unnamed: C1.1, U$2.P$6 (FILTER)
unnamed: U$2.P$3 (IP-), U$2.P$4 (IP-), U$5.P$2
unnamed: U$1.ADCINP, U$1.MUXOUTP
unnamed: U$1.ADCINN, U$1.MUXOUTN
unnamed: U$14.P$2, U$15.P$3 (IP-), U$15.P$4 (IP-)
unnamed: U$6.P$2, U$13.P$3 (IP-), U$13.P$4 (IP-)
unnamed: C6.1, U$15.P$6 (FILTER)
unnamed: U$7.P$2, U$8.P$3 (IP-), U$8.P$4 (IP-)
unnamed: C8.1, U$8.P$6 (FILTER)
unnamed: C4.1, U$13.P$6 (FILTER)
unnamed: F1.3 (2), U$4.P$1, U$4.P$2, U$4.P$3
unnamed: F2.3 (2), U$2.P$1 (IP+), U$2.P$2 (IP+)
unnamed: C11.1, U$11.P$6 (FILTER)
unnamed: U$11.P$3 (IP-), U$11.P$4 (IP-), U$12.P$2
unnamed: U$16.P$2, U$17.P$3 (IP-), U$17.P$4 (IP-)
unnamed: C14.1, U$17.P$6 (FILTER)
unnamed: U$18.P$2, U$19.P$3 (IP-), U$19.P$4 (IP-)
unnamed: C16.1, U$19.P$6 (FILTER)
unnamed: U$20.P$2, U$21.P$3 (IP-), U$21.P$4 (IP-)
unnamed: C18.1, U$21.P$6 (FILTER)
unnamed: F3.3 (2), U$13.P$1 (IP+), U$13.P$2 (IP+)
unnamed: R4.1, U1.21 (CH14)
unnamed: R10.1, U1.15 (CH8)
unnamed: F6.3 (2), U$11.P$1 (IP+), U$11.P$2 (IP+)
unnamed: R7.1, U1.18 (CH11)
unnamed: R9.1, U1.16 (CH9)
unnamed: R8.1, U1.17 (CH10)
unnamed: R6.1, U1.19 (CH12)
unnamed: R5.1, U1.20 (CH13)
unnamed: R3.1, U1.22 (CH15)
unnamed: F7.3 (2), U$17.P$1 (IP+), U$17.P$2 (IP+)
unnamed: F8.3 (2), U$19.P$1 (IP+), U$19.P$2 (IP+)
unnamed: F9.3 (2), U$21.P$1 (IP+), U$21.P$2 (IP+)
unnamed: LED1.A, R3.2
unnamed: LED2.A, R4.2
unnamed: LED3.A, R5.2
unnamed: LED4.A, R6.2
unnamed: LED5.A, R7.2
unnamed: LED6.A, R8.2
unnamed: LED7.A, R9.2
unnamed: LED8.A, R10.2
PWM0: 2PIN_2.P$1, U1.6 (CH0)
PWM1: 2PIN_3.P$1, U1.7 (CH1)
PWM2: 2PIN_11.P$1, U1.8 (CH2)
PWM3: 2PIN_4.P$1, U1.9 (CH3)
PWM4: 2PIN_6.P$1, U1.10 (CH4)
PWM5: 2PIN_7.P$1, U1.11 (CH5)
PWM6: 2PIN_8.P$1, U1.12 (CH6)
PWM7: 2PIN_9.P$1, U1.13 (CH7)
SCL: 2PIN_1.P$2, U1.26 (SCL), U$1.SCL
SDA: 2PIN_1.P$1, U1.27 (SDA), U$1.SDA
VBAT: F1.1, F2.1, F3.1, F4.1, F5.1, F6.1, F7.1, F8.1, F9.1

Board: 2 copper layers, 71 parts (0 on the bottom side), 63 nets, no tracks yet.

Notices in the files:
parts and their libraries:
SparkFun-DigitalIC: Licensing: Creative Commons ShareAlike 4.0 International - https://creativecommons.org/licenses/by-sa/4.0
